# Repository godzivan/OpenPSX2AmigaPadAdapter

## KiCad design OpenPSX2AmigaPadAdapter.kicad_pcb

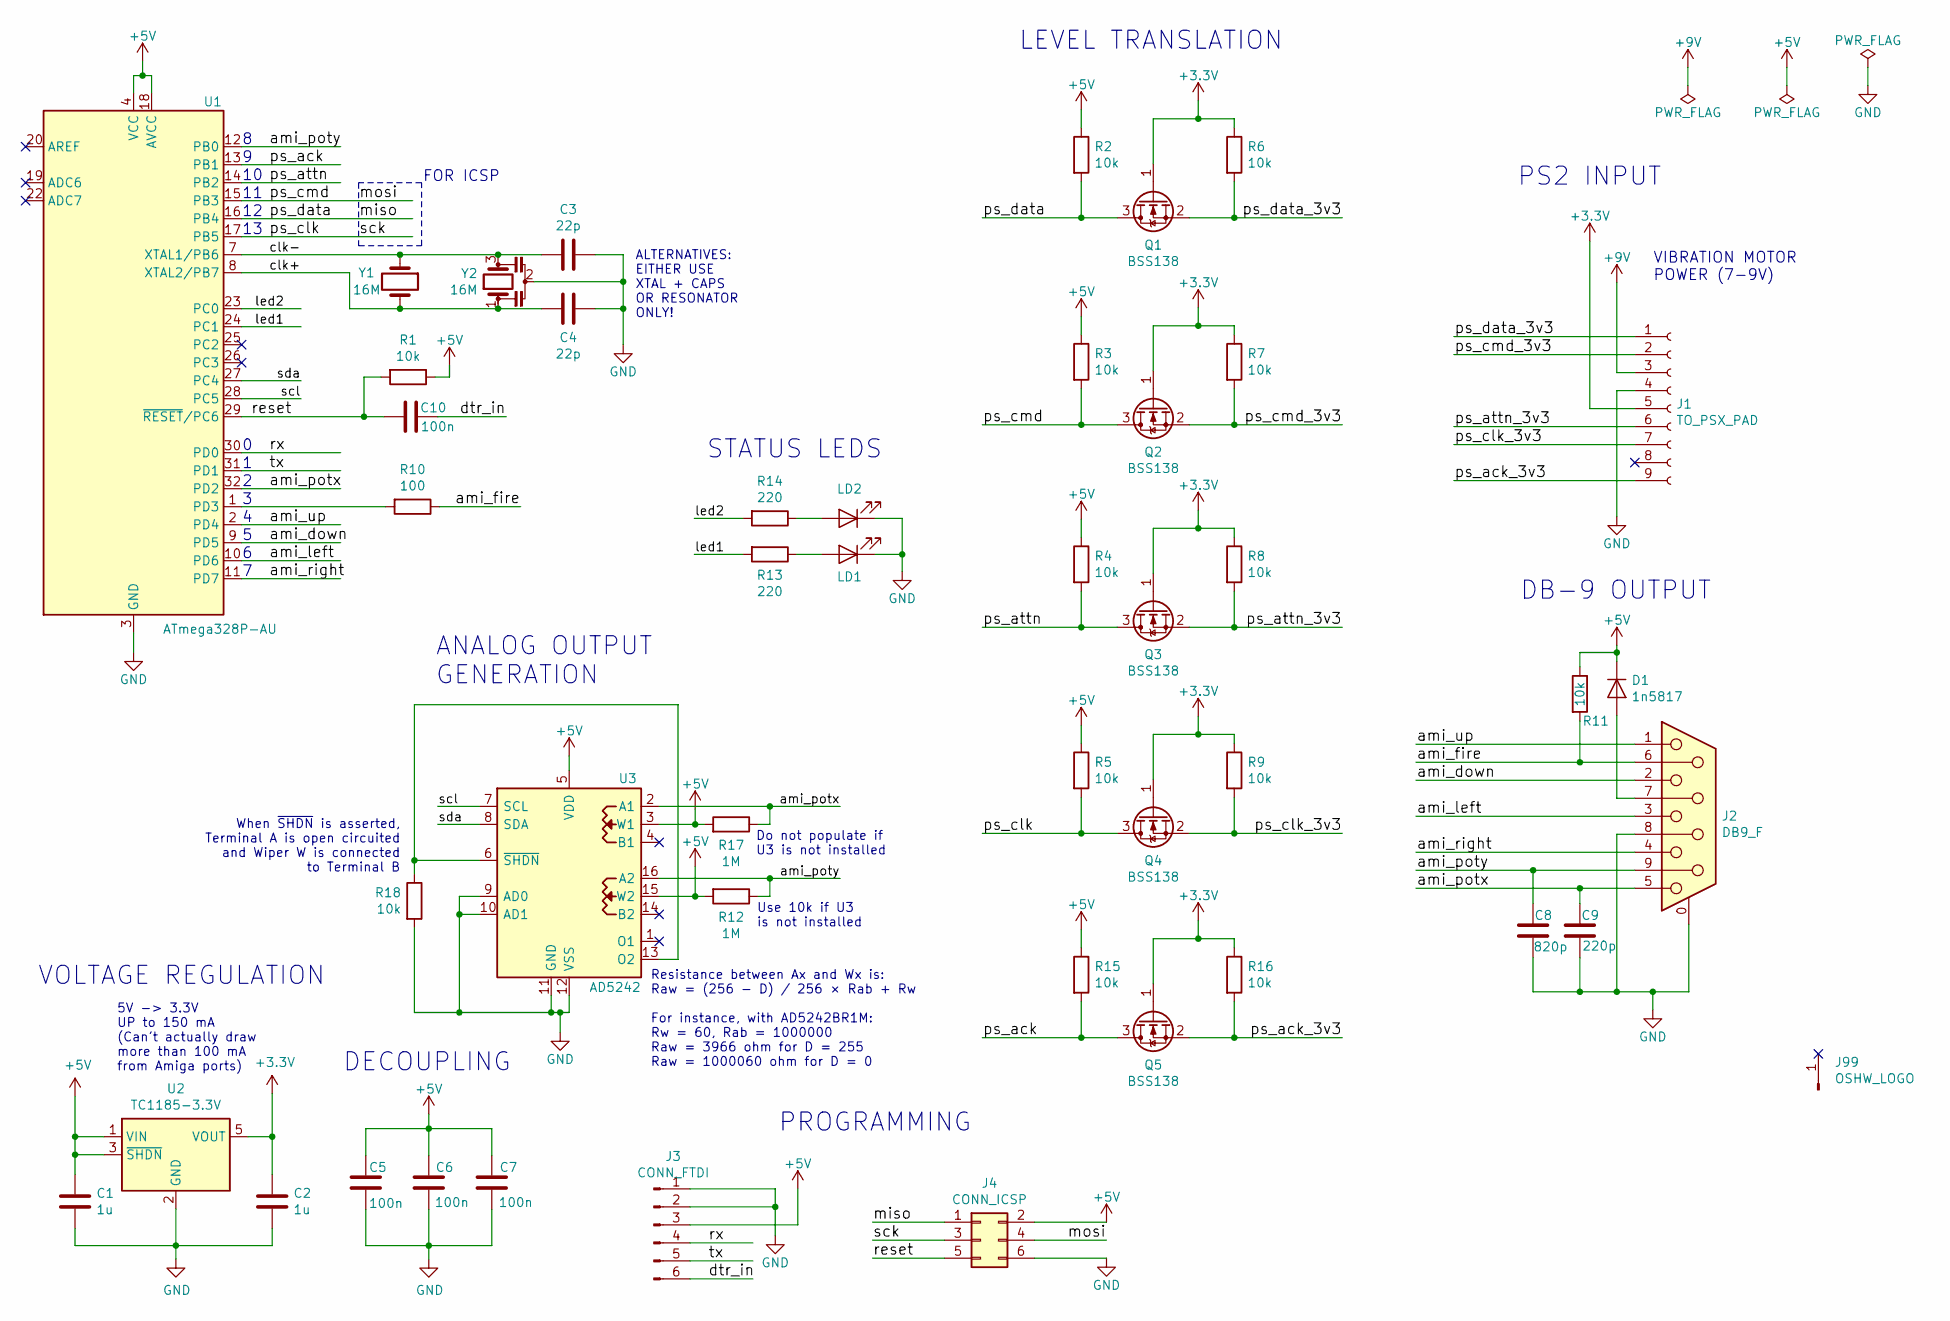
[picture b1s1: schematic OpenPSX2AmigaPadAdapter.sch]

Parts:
C1, C2: 1u; C_0805_2012Metric_Pad1.15x1.40mm_HandSolder
C3, C4: 22p; C_0805_2012Metric_Pad1.15x1.40mm_HandSolder
C5, C6, C7, C10: 100n; C_0805_2012Metric_Pad1.15x1.40mm_HandSolder
C8: 820p; C_0805_2012Metric_Pad1.15x1.40mm_HandSolder
C9: 220p; C_0805_2012Metric_Pad1.15x1.40mm_HandSolder
D1: 1n5817; D_SMA
J1: TO_PSX_PAD; PSX_Pad_Connector
J2: DB9_F; DB_9F
J3: CONN_FTDI; PinHeader_1x06_P2.54mm_Vertical
J4: CONN_ICSP; PinHeader_2x03_P2.54mm_Vertical
J99: OSHW_LOGO; OSHW-Logo_5.7x6mm_Copper
LD1, LD2: LED; LED_0805_2012Metric_Pad1.15x1.40mm_HandSolder
Q1, Q2, Q3, Q4, Q5: BSS138; SOT-23_Handsoldering
R1, R2, R3, R4, R5, R6, R7, R8, R9, R11, R15, R16, R18: 10k; R_0805_2012Metric_Pad1.15x1.40mm_HandSolder
R10: 100; R_0805_2012Metric_Pad1.15x1.40mm_HandSolder
R12, R17: 1M; R_0805_2012Metric_Pad1.15x1.40mm_HandSolder
R13, R14: 220; R_0805_2012Metric_Pad1.15x1.40mm_HandSolder
U1: ATmega328P-AU; TQFP-32_7x7mm_P0.8mm
U2: TC1185-3.3V; SOT-23-5_HandSoldering
U3: AD5242; SOIC-16_3.9x9.9mm_P1.27mm
Y1: 16M; Crystal_HC49-U_Vertical
Y2: 16M; Resonator_SMD_muRata_CSTxExxV

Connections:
+3V3: C2.1, J1.5, Q1.1 (G), Q2.1 (G), Q3.1 (G), Q4.1 (G), Q5.1 (G), R6.1, R7.1, R8.1, R9.1, R16.1, U2.5 (VOUT)
+5V: C1.1, C5.2, C6.2, C7.2, D1.1 (K), J3.3, J4.2, R1.1, R2.1, R3.1, R4.1, R5.1, R11.1, R12.2, R15.1, R17.2, U1.4 (VCC), U1.6 (VCC), U1.18 (AVCC), U2.1 (VIN), U2.3 (~SHDN), U3.3 (W1), U3.5 (VDD), U3.15 (W2)
/ami_down: J2.2, U1.9 (PD5)
/ami_fire: J2.6, R10.1, R11.2
/ami_left: J2.3, U1.10 (PD6)
/ami_potx: C9.1, J2.5, R17.1, U1.32 (PD2), U3.2 (A1)
/ami_poty: C8.1, J2.9, R12.1, U1.12 (PB0), U3.16 (A2)
/ami_right: J2.4, U1.11 (PD7)
/ami_up: J2.1, U1.2 (PD4)
/clk+: C4.2, U1.8 (XTAL2/PB7), Y1.2, Y2.1
/clk-: C3.2, U1.7 (XTAL1/PB6), Y1.1, Y2.3
/dtr_in: C10.1, J3.6
/led1: R13.2, U1.24 (PC1)
/led2: R14.2, U1.23 (PC0)
/miso: J4.1, Q1.3 (D), R2.2, U1.16 (PB4)
/mosi: J4.4, Q2.3 (D), R3.2, U1.15 (PB3)
/ps_ack: Q5.3 (D), R15.2, U1.13 (PB1)
/ps_ack_3v3: J1.9, Q5.2 (S), R16.2
/ps_attn: Q3.3 (D), R4.2, U1.14 (PB2)
/ps_attn_3v3: J1.6, Q3.2 (S), R8.2
/ps_clk: J4.3, Q4.3 (D), R5.2, U1.17 (PB5)
/ps_clk_3v3: J1.7, Q4.2 (S), R9.2
/ps_cmd_3v3: J1.2, Q2.2 (S), R7.2
/ps_data_3v3: J1.1, Q1.2 (S), R6.2
/reset: C10.2, J4.5, R1.2, U1.29 (~RESET~/PC6)
/rx: J3.4, U1.30 (PD0)
/scl: U1.28 (PC5), U3.7 (SCL)
/sda: U1.27 (PC4), U3.8 (SDA)
/tx: J3.5, U1.31 (PD1)
GND: C1.2, C2.2, C3.1, C4.1, C5.1, C6.1, C7.1, C8.2, C9.2, J1.4, J2.0 (PAD), J2.8, J3.1, J3.2, J4.6, LD1.1 (K), LD2.1 (K), R18.2, U1.3 (GND), U1.5 (GND), U1.21 (GND), U2.2 (GND), U3.9 (AD0), U3.10 (AD1), U3.11 (GND), U3.12 (VSS), Y2.2
unnamed: D1.2 (A), J2.7
unnamed: LD1.2 (A), R13.1
unnamed: LD2.2 (A), R14.1
unnamed: R10.2, U1.1 (PD3)
unnamed: R18.1, U3.6 (~SHDN~), U3.13 (O2)

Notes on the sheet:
VIBRATION MOTOR POWER (7-9V)
FOR ICSP
ALTERNATIVES: EITHER USE XTAL + CAPS OR RESONATOR ONLY!
When ~SHDN~ is asserted, Terminal A is open circuited and Wiper W is connected to Terminal B
5V -> 3.3V UP to 150 mA (Can't actually draw more than 100 mA from Amiga ports)
VOLTAGE REGULATION
DECOUPLING
ANALOG OUTPUT GENERATION
PROGRAMMING
STATUS LEDS
PS2 INPUT
DB-9 OUTPUT
LEVEL TRANSLATION
Resistance between Ax and Wx is: Raw = (256 − D) / 256 × Rab + Rw For instance, with AD5242BR1M: Rw = 60, Rab = 1000000 Raw = 3966 ohm for D = 255 Raw = 1000060 ohm for D = 0
Use 10k if U3 is not installed
Do not populate if U3 is not installed

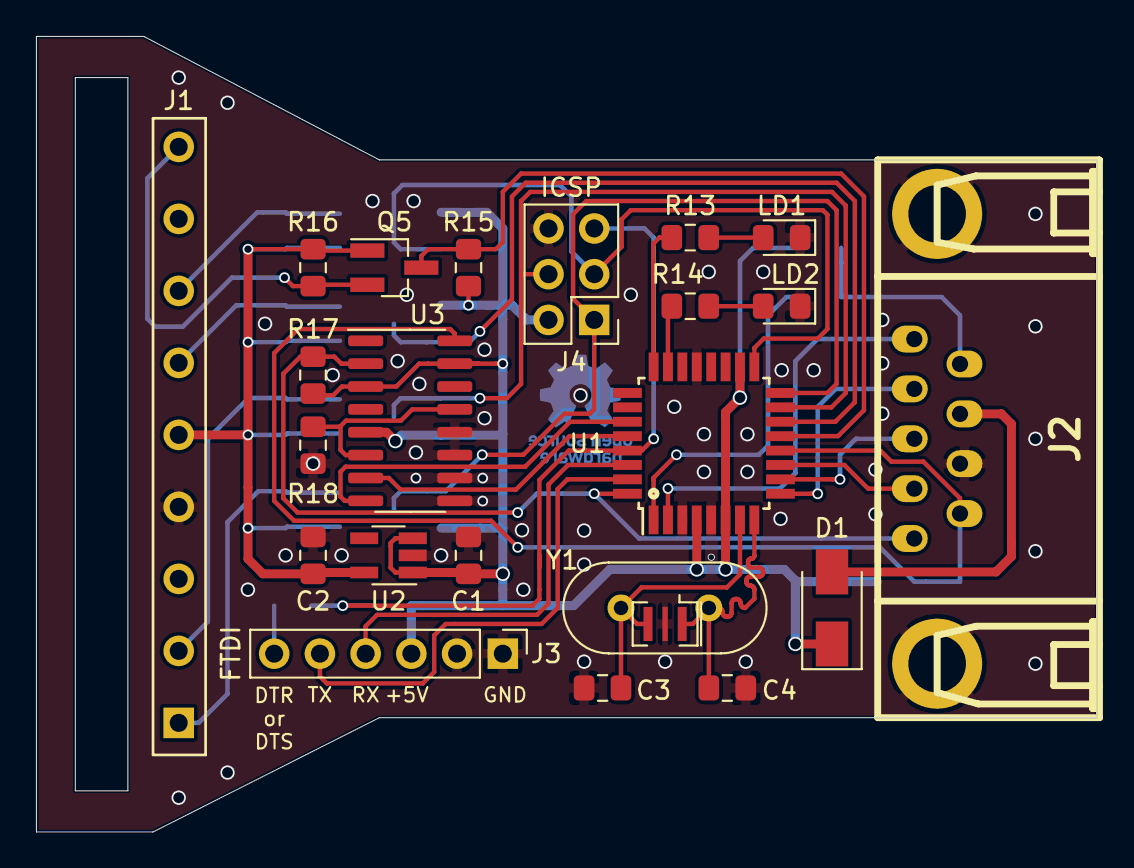
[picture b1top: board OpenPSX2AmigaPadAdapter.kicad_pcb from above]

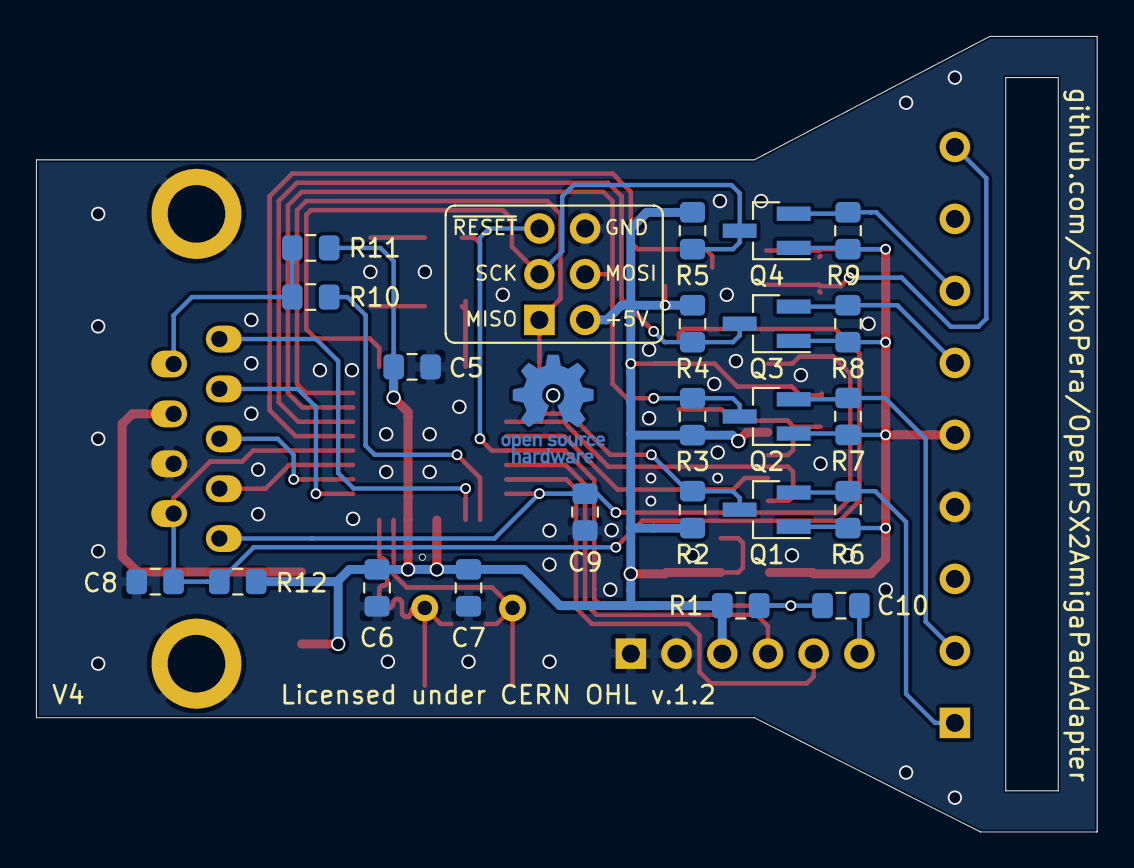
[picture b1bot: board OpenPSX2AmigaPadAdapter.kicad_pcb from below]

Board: 2 copper layers, 58.9 x 44.2 mm, 46 parts (23 on the bottom side), 35 nets.

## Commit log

2020-04-23 Begin adding analog output support to firmware
2020-04-23 Add note about R12
2020-04-23 Ready for V4
2020-04-23 Output compensation table
2020-04-23 PCB modifications for analog support are complete
2020-04-23 Add docs
2020-04-23 Fix component naming
2020-04-23 Update analog value table
2020-04-23 Update schematics for analog output support. PCB TBD.
2020-04-23 Swap Ax/Wx It probably doesn't matter, but I feel better knowing that potx/y are "isolated" when AD5242 is in shutdown
2020-04-23 Add 4 different analog mappings
2020-04-24 Make schematics clearer
2020-04-24 Fix analog mode button 3
2020-04-25 Add readback of values sent to AD5242 for debugging
2020-04-26 Make EEPROM support optional Not much useful, but since I'd done this for a development emergency, I just thought I'd make it official
2020-05-08 Fix factory reset
2020-05-08 Fix factory reset for slow-startup controllers and add Test Mode
2020-05-08 Avoid triggering axes inversion more than once per press
2020-05-08 Fully isolate ANALOG_SUPPORT stuff so that we can build for older boards
2020-05-25 Disable analog support by default
2020-05-25 Use const where possible
2020-05-25 Really make test mode optional
2020-05-25 Avoid spurious 0V state when entering CD32 mode
2020-05-25 Do not disable output on clock pin twice
2020-05-25 Enable INT1 ASAP when switching to CD32 mode, to avoid missing the first clock edge
2020-05-25 Restore DISABLE_TEST This somehow disappeared in 4aed0cf37c25a0b9b719b2759d31e5fa83434131 :(
2020-05-25 Add capability to inhibit CD32 mode
2020-07-22 Only switch PIN_BTNREGOUT to OUTPUT in ISR once

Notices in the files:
OpenPSX2AmigaPadAdapter.kicad_pcb:
Licensed under CERN OHL v.1.2
